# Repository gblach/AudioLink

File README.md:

# AudioLink

AudioLink is a USB and Bluetooth LE Audio receiver with line outputs. Connect it to an amplifier
or active speakers and play music from a computer, a phone or an Auracast broadcast.

https://github.com/user-attachments/assets/b21d6140-ebe1-4f9f-b59c-d1f0c58b71b1

## Features

- **Three sources:** a computer over USB, a phone over Bluetooth LE Audio, or an Auracast
  broadcast.
- **Two 6.35 mm line outputs:** unbalanced stereo or balanced.
- **5-band equalizer**, set from the companion app.
- **Four LEDs that follow the music:** they jump up on loud sounds and fade out in quiet parts.
- **Firmware updates** from the app, over USB or over SWD.
- **Powered from USB-C.** No driver is needed on the computer.

## Hardware

| Part          | Component                                     |
| ------------- | --------------------------------------------- |
| Module        | MinewSemi MS45SF1 (nRF5340, Bluetooth LE)     |
| DAC           | TI PCM5242                                    |
| Output buffer | TI OPA1678                                    |
| LEDs          | 4 x WS2812                                    |
| Outputs       | 2 x 6.35 mm jack (J1, J2)                     |
| Power         | USB-C (J3)                                    |
| PCB           | 4 layers, 100 x 56 mm, all parts on the top   |

## Repository layout

| Path        | Contents                                                             |
| ----------- | -------------------------------------------------------------------- |
| `firmware/` | Zephyr / nRF Connect SDK firmware for both nRF5340 cores             |
| `app/`      | Flutter app (Android, Linux): equalizer, LEDs, firmware update       |
| `pcb/`      | KiCad schematic and PCB, BOM export script, fabrication files        |
| `assets/`   | Release files: firmware hex and DFU images, Android APK; images      |

## Release files

Current release: **0.1.3**.

| File                                                                | Use                                                     |
| ------------------------------------------------------------------- | ------------------------------------------------------- |
| [AudioLink-0.1.3.apk](assets/AudioLink-0.1.3.apk)                   | Android app                                             |
| [AudioLink-0.1.3-dfu.zip](assets/AudioLink-0.1.3-dfu.zip)           | Firmware update over Bluetooth or USB                   |
| [AudioLink-0.1.3-app-core.hex](assets/AudioLink-0.1.3-app-core.hex) | New board over SWD, application core (MCUboot and app)  |
| [AudioLink-0.1.3-net-core.hex](assets/AudioLink-0.1.3-net-core.hex) | New board over SWD, network core (bootloader and radio) |

The version is set in `firmware/VERSION`. The commands below write it as `<ver>`.

## Quick start

1. Plug a USB-C cable into the board.
2. Connect the outputs:
   - **Stereo cable:** use J1 only.
   - **Balanced:** J1 for left, J2 for right. Plugging anything into J2 switches the board to
     balanced mode.
3. Play some music:
   - **From a computer:** select the "AudioLink" sound card.
   - **From a phone:** pair "AudioLink" in the Bluetooth settings. The phone must support LE
     Audio (classic Bluetooth A2DP and iPhones are not supported).
4. Install the [Android app](assets/AudioLink-0.1.3.apk) to set the equalizer and the LEDs.

Without a connected phone, the board joins the first Auracast broadcast it finds.

When several sources play at once, the board picks one:

> USB > phone > Auracast broadcast

## App

The app connects to the board over Bluetooth LE. It sets the equalizer, the LED brightness and
the LED theme, and installs the firmware bundled in the app.

## LEDs

The four LEDs change with the dynamics of the music. They light up at once on a louder sound,
fade over about a second and go dark when the music stops. The level is measured before the
volume, so turning the volume down does not dim them.

In the app you can set:

- **Brightness:** the maximum brightness, from 0% (off) to 100%.
- **Theme:** one of four color pairs.

The small blue LED D5 is the power indicator.

See [LEDs](firmware/README.md#leds) in the firmware README for the LED positions and the
Bluetooth characteristics.

## Flashing and updating

### New board

A new board is flashed over SWD (J-Link on the 10-pin header J4), network core first:

```
nrfutil device recover
nrfutil device program --firmware assets/AudioLink-<ver>-net-core.hex --core Network \
    --options chip_erase_mode=ERASE_ALL
nrfutil device program --firmware assets/AudioLink-<ver>-app-core.hex --core Application \
    --options chip_erase_mode=ERASE_ALL
nrfutil device reset
```

### Board with AudioLink firmware

No probe is needed. Use one of:

- **App:** the update button in the app bar (firmware bundled in the app).
- **nRF Connect Device Manager:** upload `AudioLink-<ver>-dfu.zip` from a paired phone.
- **USB:** `uv run --script firmware/scripts/usb_update.py assets/AudioLink-<ver>-dfu.zip`

The bootloader refuses firmware older than the one running.

## Building

### Firmware

Requirements:

- `nrfutil` with the nRF Connect SDK installed by `nrfutil sdk-manager`
- `just`
- `uv`, for the USB update script

Copy `firmware/.env.example` to `firmware/.env` (not in git) and set the SDK version:

```
NCS_VERSION=v<x.y.z>
# Optional, $HOME/ncs/$NCS_VERSION by default
NCS_DIR=$HOME/ncs/$NCS_VERSION
```

Then, in `firmware/`:

```
just keys    # once, creates the signing keys
just build
```

See [firmware/README.md](firmware/README.md) for all commands, the output modes, LEDs, the
Bluetooth settings service and the update process.

> [!WARNING]
> The signing keys in `firmware/keys/` are not in git. Keep a backup: without them, boards in the
> field can only be updated over SWD.

### App

Bundle the current firmware into the app, then build it with Flutter:

```
cd firmware && just app-firmware
cd ../app && flutter build apk --target-platform android-arm64
```

### Release files

| Copy from                                           | To                               |
| --------------------------------------------------- | -------------------------------- |
| `firmware/build/app/dfu_application.zip`            | `assets/AudioLink-<ver>-dfu.zip` |
| `app/build/app/outputs/flutter-apk/app-release.apk` | `assets/AudioLink-<ver>.apk`     |

The hex files are merged from the build output, see
[Release files](firmware/README.md#release-files) in the firmware README. Then update the links
in [Release files](#release-files) above to the new version.

## PCB

The KiCad project is `pcb/AudioLink.kicad_pro`. A PDF of the schematic is in
`pcb/fab/AudioLink-schematic.pdf`.

- `pcb/fab/` has the fabrication and assembly files, with notes on part substitutions in
  `pcb/fab/README-fab.txt`.
- `pcb/export_bom.py` regenerates `pcb/fab/AudioLink-BOM.csv` from the schematic.

### Enclosure

The board fits the CamdenBoss
[CBHEX1-06-WH](https://www.camdenboss.com/camden-boss/cbhex1-06-wh-hex-box-iot-enclosure-with-6-vented-panels,-white/c-23/p-24194)
Hex-Box enclosure:

- ABS, 146 x 130 x 45 mm outside, 122.5 x 125.5 x 34.5 mm inside
- six removable vented side panels

The jacks J1 and J2 overhang the board edge so they reach a side panel.

## License

| Part                      | License                                                                                              |
| ------------------------- | ---------------------------------------------------------------------------------------------------- |
| Firmware, app and scripts | MIT, see [LICENSE](LICENSE)                                                                          |
| PCB design in `pcb/`      | CERN Open Hardware Licence v2 - Strongly Reciprocal (CERN-OHL-S-2.0), see [pcb/LICENSE](pcb/LICENSE) |

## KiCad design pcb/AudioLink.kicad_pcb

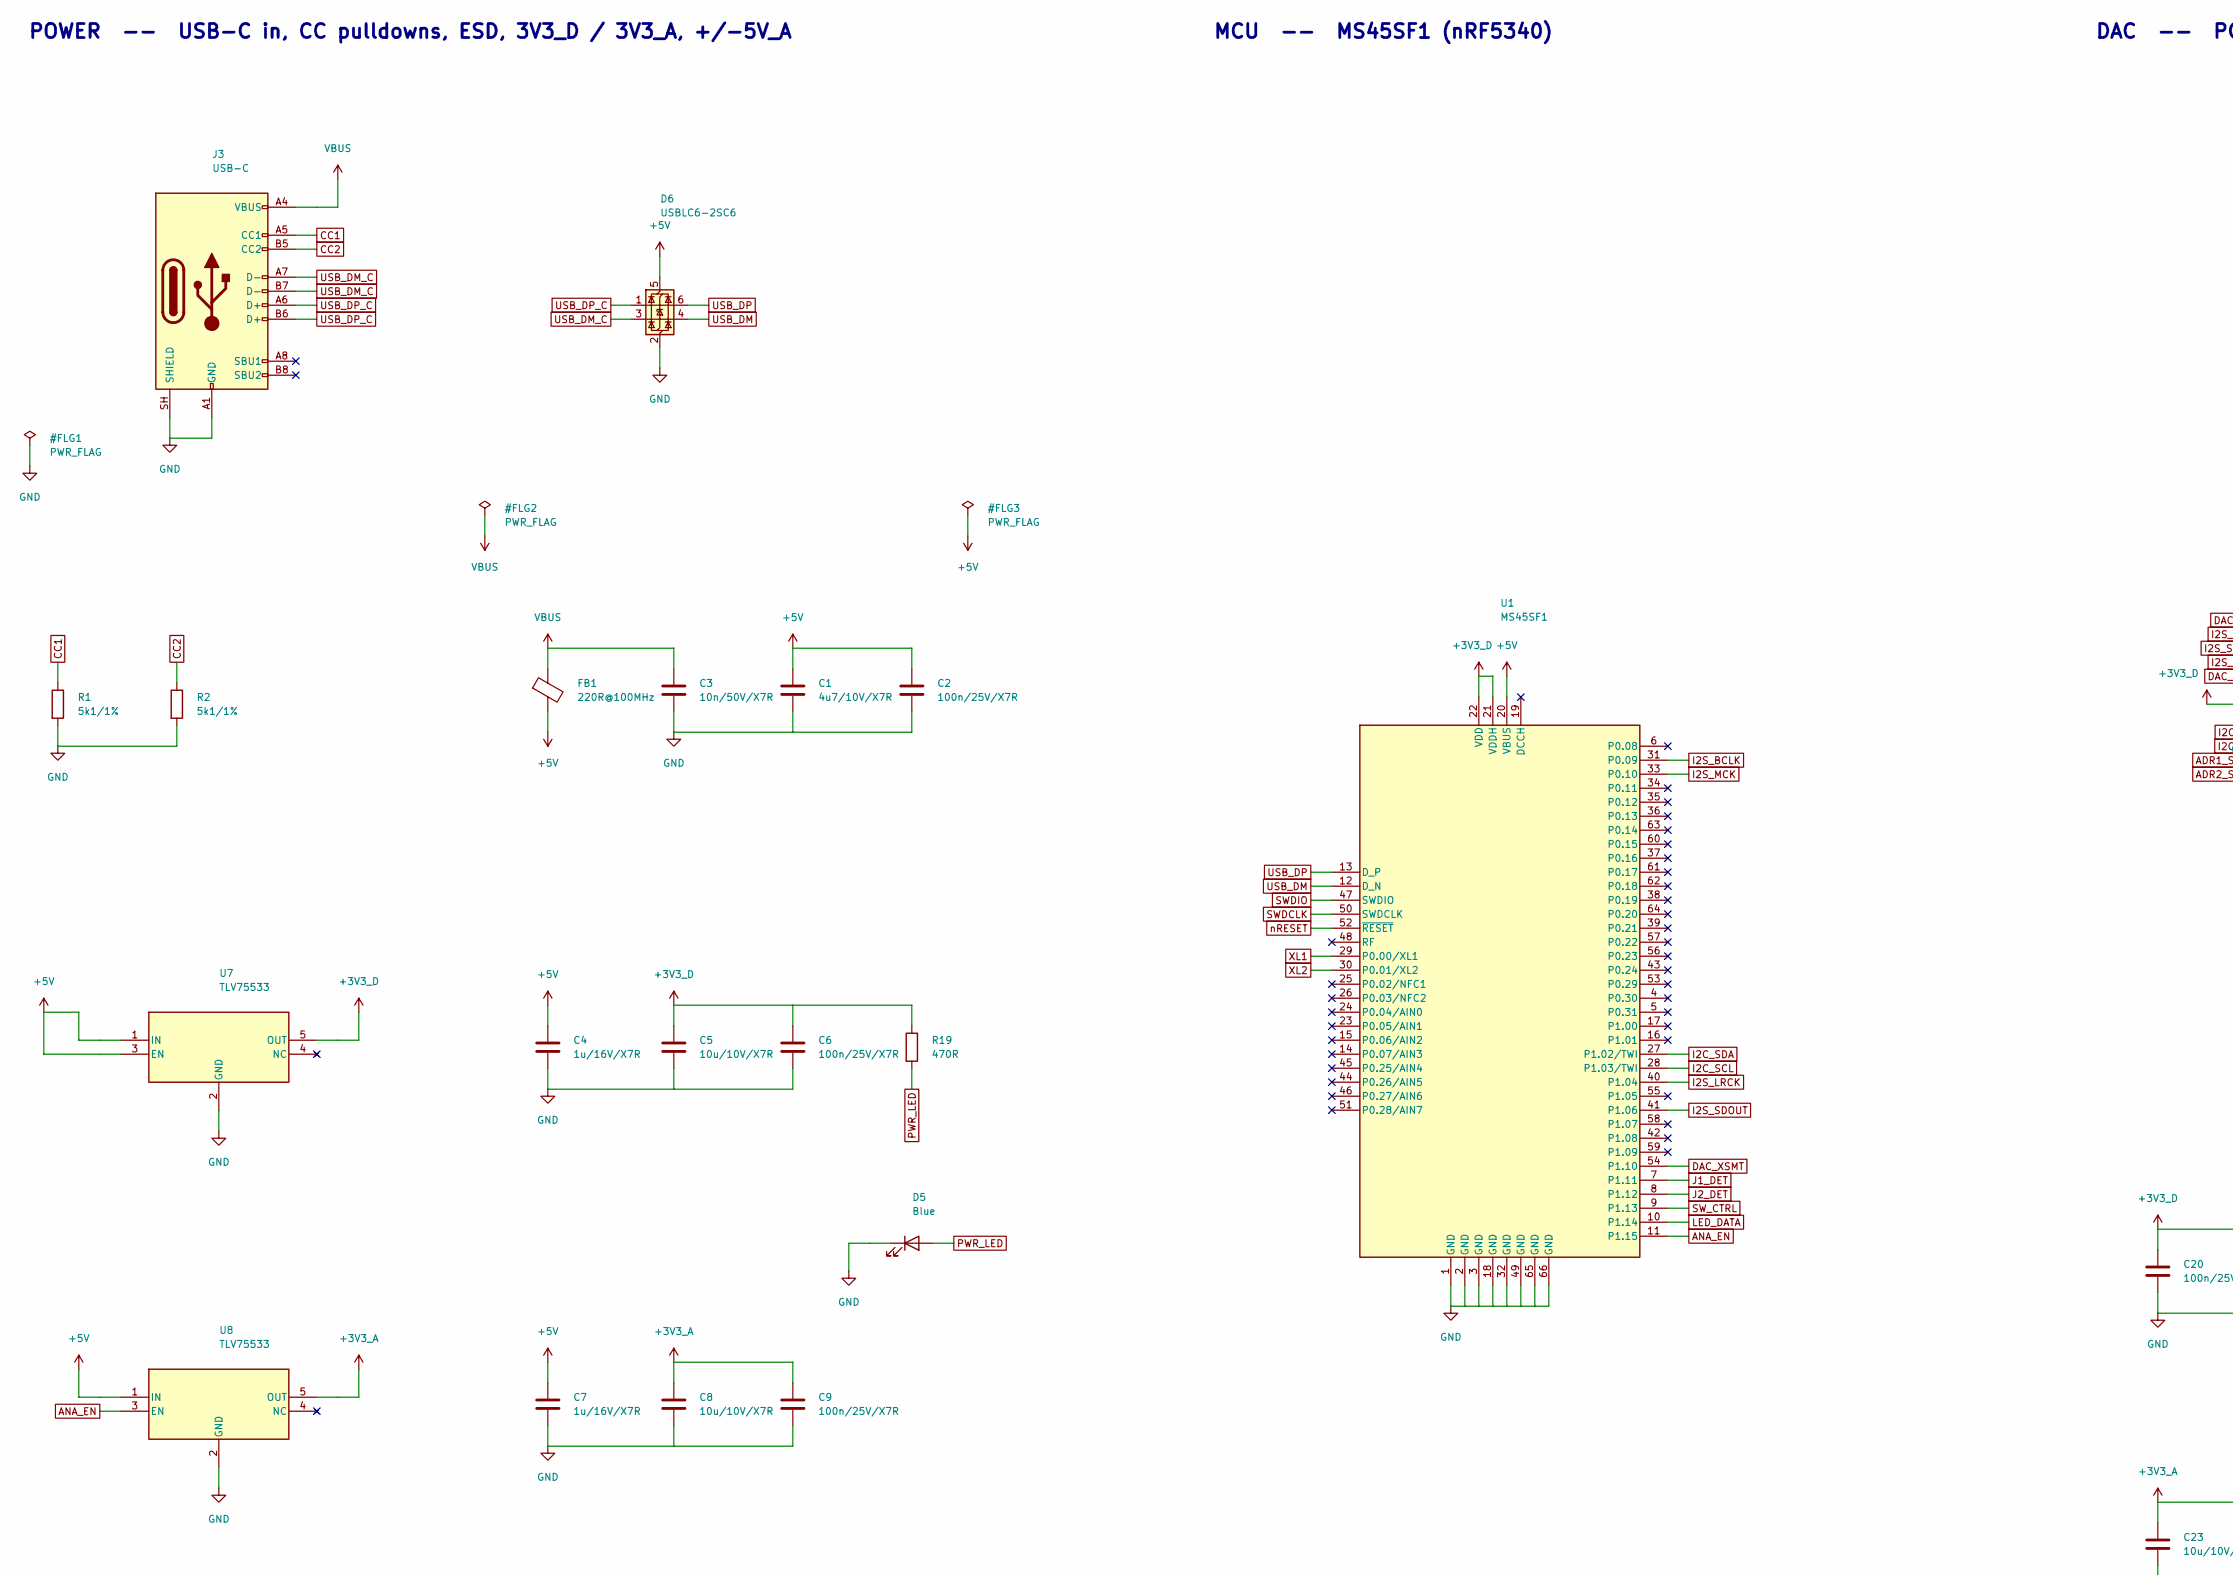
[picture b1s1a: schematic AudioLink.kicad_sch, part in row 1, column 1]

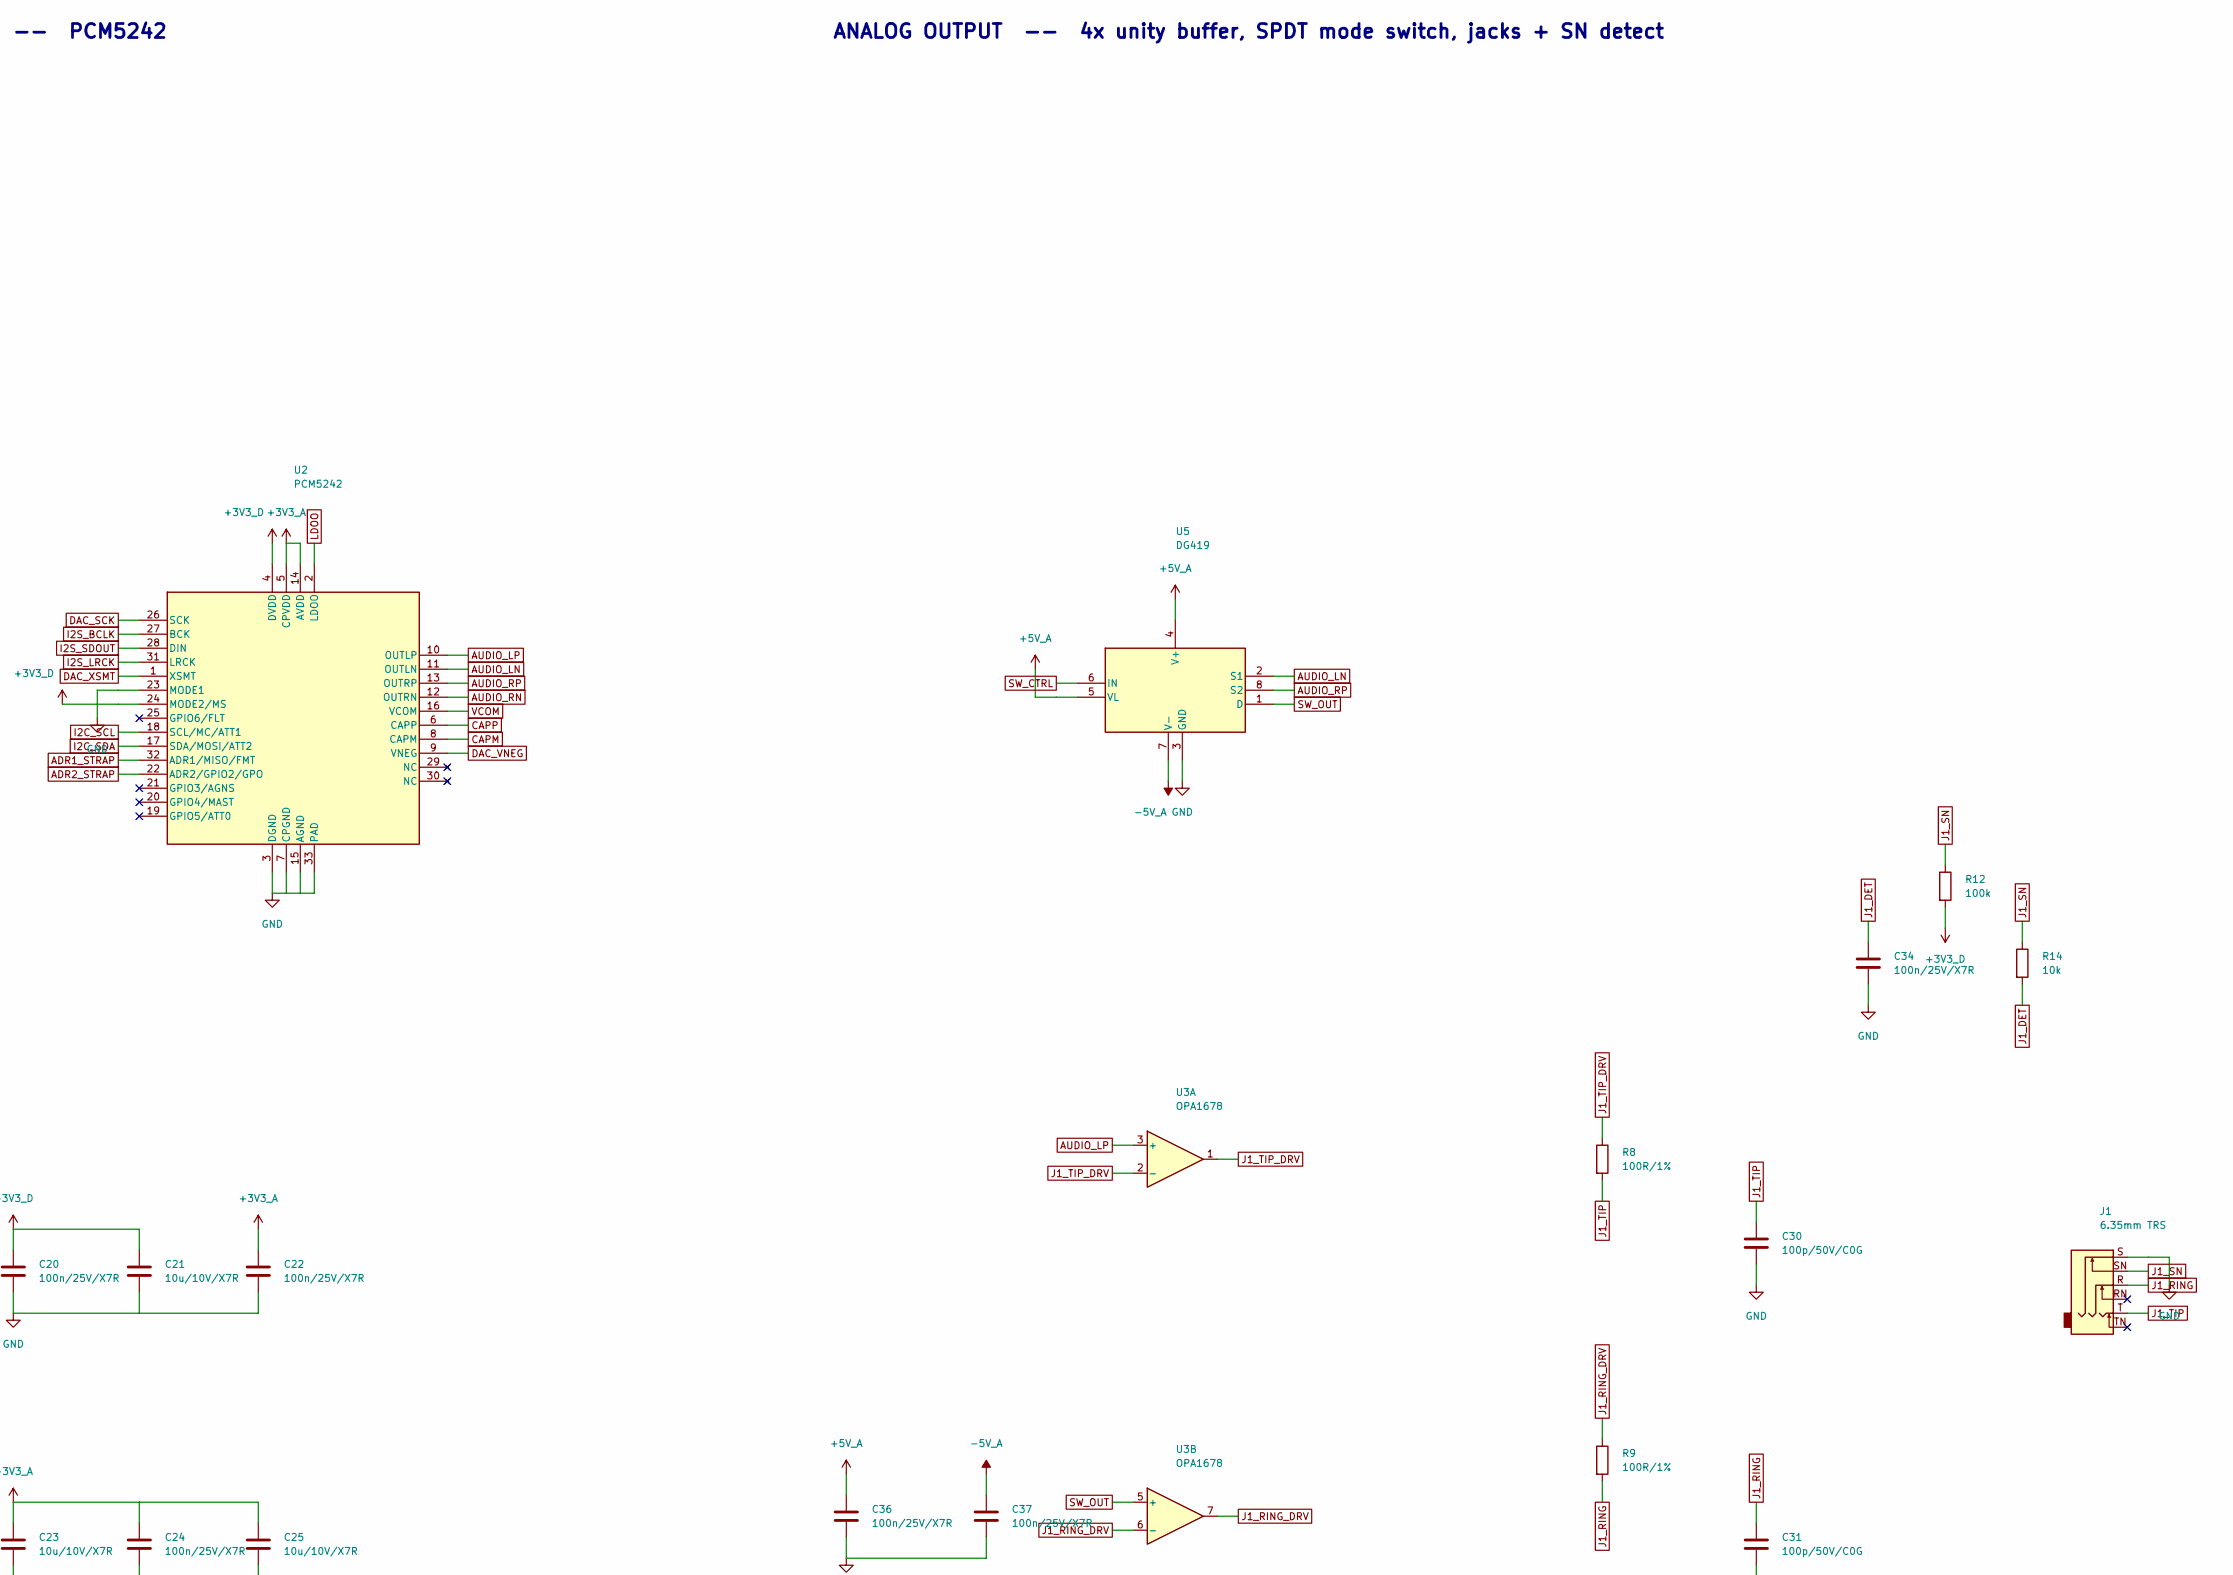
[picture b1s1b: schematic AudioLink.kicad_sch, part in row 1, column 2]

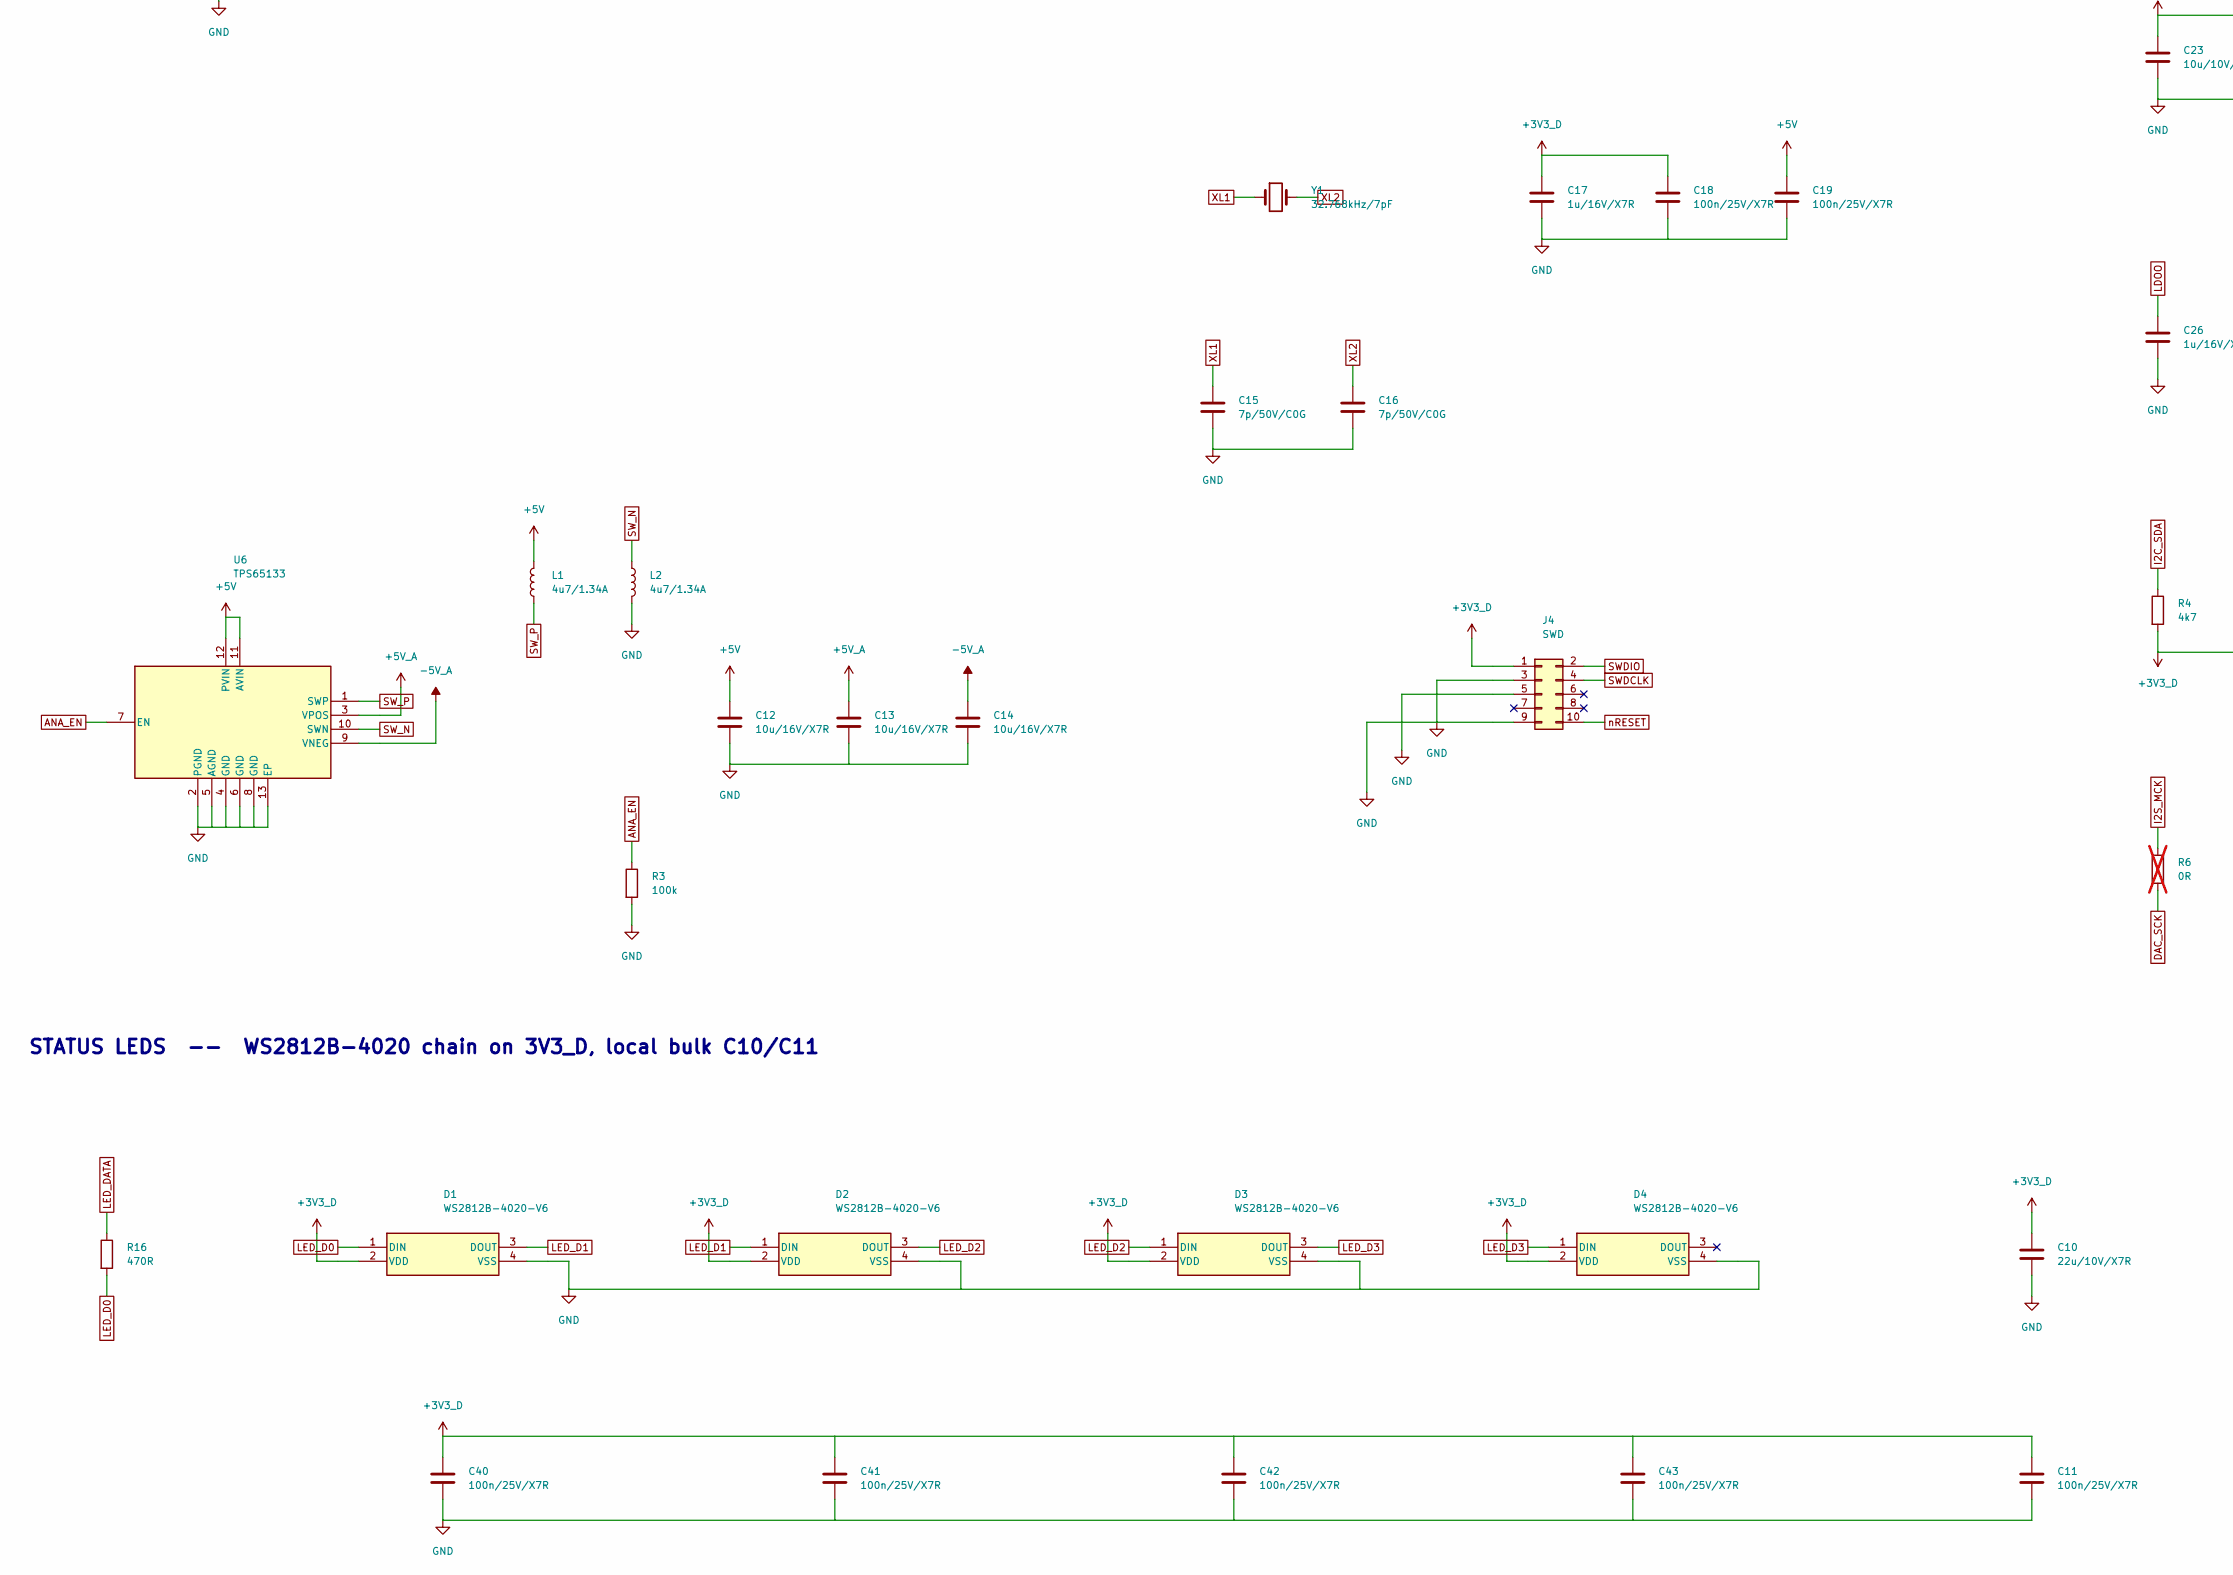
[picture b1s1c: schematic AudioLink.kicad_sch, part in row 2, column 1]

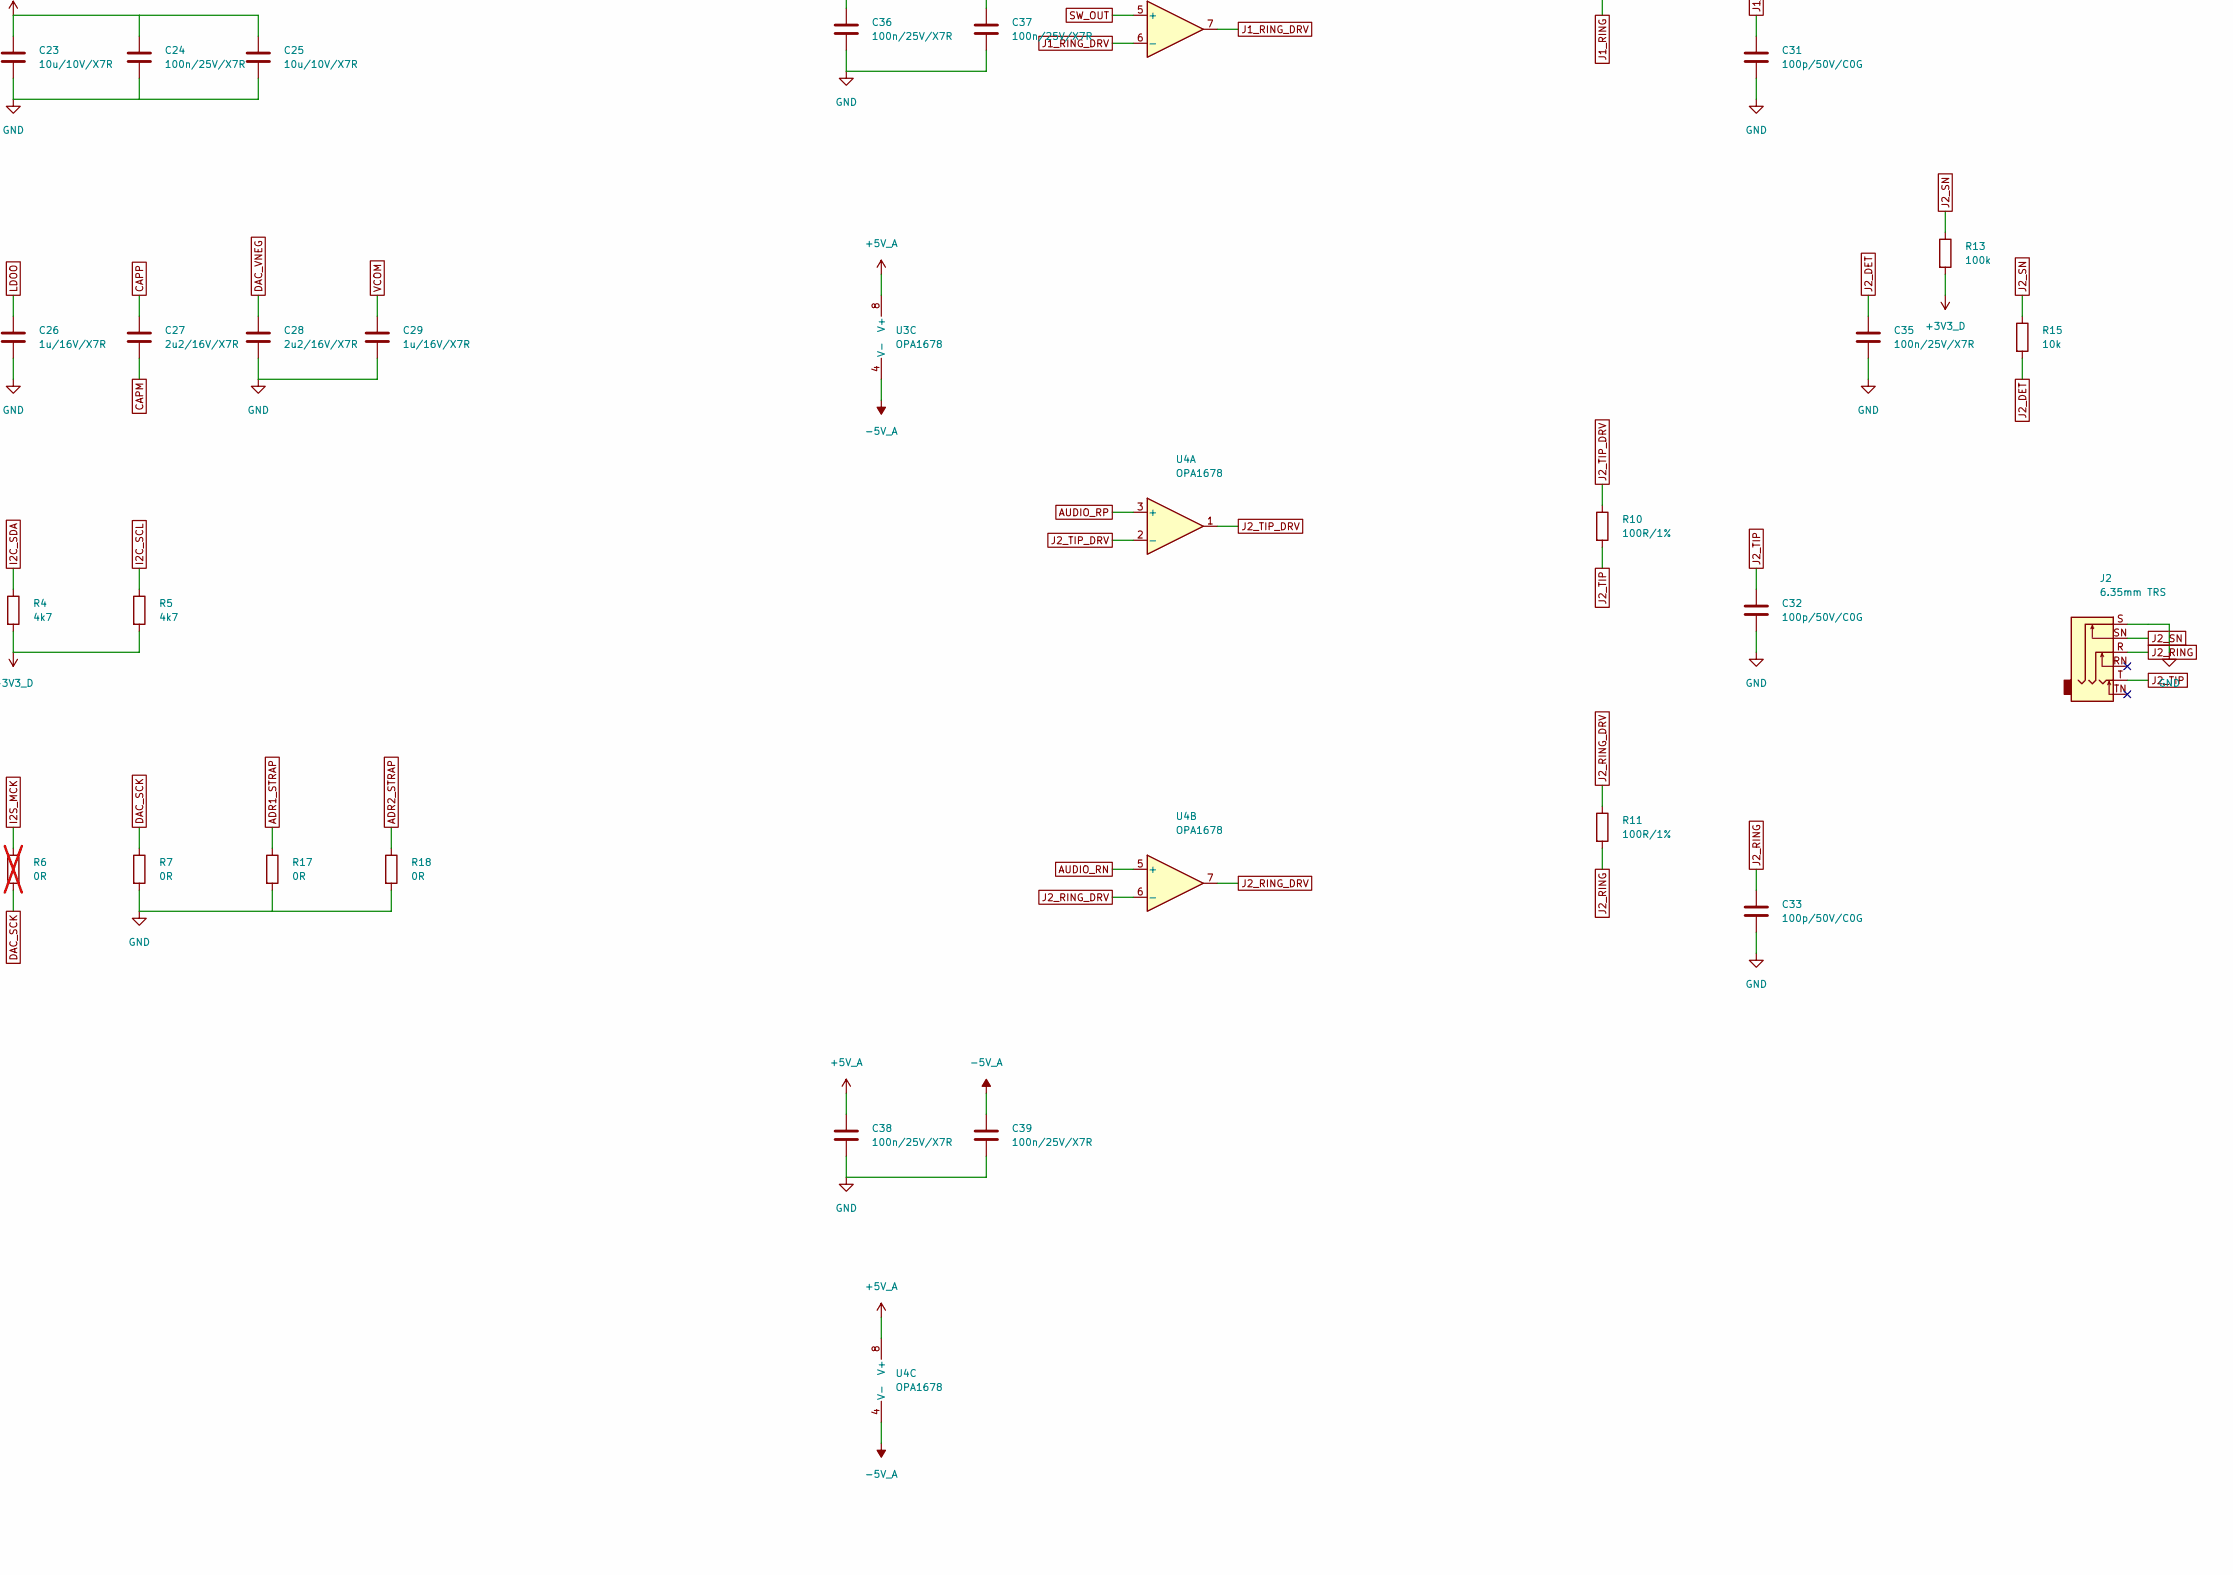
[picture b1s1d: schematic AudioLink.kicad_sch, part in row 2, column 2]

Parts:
C1: 4u7/10V/X7R; C_0805_2012Metric
C2, C6, C9, C11, C18, C19, C20, C22, C24, C34, C35, C36, C37, C38, C39, C40, C41, C42, C43: 100n/25V/X7R; C_0603_1608Metric
C3: 10n/50V/X7R; C_0603_1608Metric
C4, C7, C17, C26, C29: 1u/16V/X7R; C_0603_1608Metric
C5, C8, C21, C23, C25: 10u/10V/X7R; C_0805_2012Metric
C10: 22u/10V/X7R; C_0805_2012Metric
C12, C13, C14: 10u/16V/X7R; C_0805_2012Metric
C15, C16: 7p/50V/C0G; C_0603_1608Metric
C27, C28: 2u2/16V/X7R; C_0603_1608Metric
C30, C31, C32, C33: 100p/50V/C0G; C_0603_1608Metric
D1, D2, D3, D4: WS2812B-4020-V6; LED_WS2812B-4020; MPN WS2812B-4020-V6
D5: Blue; LED_0603_1608Metric; MPN GL0603UB01
D6: USBLC6-2SC6; SOT-23-6; MPN USBLC6-2SC6
FB1: 220R@100MHz; R_0603_1608Metric; MPN BLM18PG221SN1D
J1, J2: 6.35mm TRS; Jack_6.35mm_Neutrik_NRJ6HM-1_TrimCrtYd; MPN NRJ6HM-1
J3: USB-C; USB_C_Receptacle_HCTL_HC-TYPE-C-16P-01A; MPN TYPE-C 16PIN 2MD(073)
J4: SWD; PinHeader_2x05_P1.27mm_Vertical; MPN 62201021621
L1, L2: 4u7/1.34A; L_Bourns-SRN4018; MPN SWPA4020S4R7MT
R1, R2: 5k1/1%; R_0603_1608Metric
R3, R12, R13: 100k; R_0603_1608Metric
R4, R5: 4k7; R_0603_1608Metric
R6: 0R; R_0603_1608Metric; not fitted
R7, R17, R18: 0R; R_0603_1608Metric
R8, R9, R10, R11: 100R/1%; R_0805_2012Metric
R14, R15: 10k; R_0603_1608Metric
R16, R19: 470R; R_0603_1608Metric
U1: MS45SF1; MinewSemi_MS45SF1; MPN MS45SF1-1Y40AIR
U2: PCM5242; VQFN-32-1EP_5x5mm_P0.5mm_EP3.15x3.15mm; MPN PCM5242RHBR
U3, U4: OPA1678; SOIC-8_3.9x4.9mm_P1.27mm; MPN OPA1678IDR
U5: DG419; SOIC-8_3.9x4.9mm_P1.27mm; MPN DG419DY-T1-E3
U6: TPS65133; WSON-12-1EP_3x3mm_P0.5mm_EP1.5x2.5mm; MPN TPS65133DPDR
U7, U8: TLV75533; SOT-23-5; MPN TLV75533PDBVR
Y1: 32.768kHz/7pF; Crystal_SMD_3215-2Pin_3.2x1.5mm; MPN FC-135 32.7680KA-A5

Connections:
+3V3_A: C8.1, C9.1, C22.1, C23.1, C24.1, C25.1, U2.5 (CPVDD), U2.14 (AVDD), U8.5 (OUT)
+3V3_D: C5.1, C6.1, C10.1, C11.1, C17.1, C18.1, C20.1, C21.1, C40.1, C41.1, C42.1, C43.1, D1.2 (VDD), D2.2 (VDD), D3.2 (VDD), D4.2 (VDD), J4.1, R4.2, R5.2, R12.2, R13.2, R19.1, U1.21 (VDDH), U1.22 (VDD), U2.4 (DVDD), U2.24 (MODE2/MS), U7.5 (OUT)
+5V: C1.1, C2.1, C4.1, C7.1, C12.1, C19.1, D6.5 (VBUS), FB1.2, L1.2, U1.20 (VBUS), U6.11 (AVIN), U6.12 (PVIN), U7.1 (IN), U7.3 (EN), U8.1 (IN)
+5V_A: C13.1, C36.1, C38.1, U3.8 (V+), U4.8 (V+), U5.4 (V+), U5.5 (VL), U6.3 (VPOS)
-5V_A: C14.1, C37.1, C39.1, U3.4 (V-), U4.4 (V-), U5.7 (V-), U6.9 (VNEG)
ADR1_STRAP: R17.1, U2.32 (ADR1/MISO/FMT)
ADR2_STRAP: R18.1, U2.22 (ADR2/GPIO2/GPO)
ANA_EN: R3.1, U1.11 (P1.15), U6.7 (EN), U8.3 (EN)
AUDIO_LN: U2.11 (OUTLN), U5.2 (S1)
AUDIO_LP: U2.10 (OUTLP), U3.3 (+)
AUDIO_RN: U2.12 (OUTRN), U4.5 (+)
AUDIO_RP: U2.13 (OUTRP), U4.3 (+), U5.8 (S2)
CAPM: C27.2, U2.8 (CAPM)
CAPP: C27.1, U2.6 (CAPP)
CC1: J3.A5 (CC1), R1.1
CC2: J3.B5 (CC2), R2.1
DAC_SCK: R6.2, R7.1, U2.26 (SCK)
DAC_VNEG: C28.1, U2.9 (VNEG)
DAC_XSMT: U1.54 (P1.10), U2.1 (XSMT)
GND: C1.2, C2.2, C3.2, C4.2, C5.2, C6.2, C7.2, C8.2, C9.2, C10.2, C11.2, C12.2, C13.2, C14.2, C15.2, C16.2, C17.2, C18.2, C19.2, C20.2, C21.2, C22.2, C23.2, C24.2, C25.2, C26.2, C28.2, C29.2, C30.2, C31.2, C32.2, C33.2, C34.2, C35.2, C36.2, C37.2, C38.2, C39.2, C40.2, C41.2, C42.2, C43.2, D1.4 (VSS), D2.4 (VSS), D3.4 (VSS), D4.4 (VSS), D5.1 (K), D6.2 (GND), J1.S, J2.S, J3.A1 (GND), J3.A12 (GND), J3.B1 (GND), J3.B12 (GND), J3.SH (SHIELD), J4.3, J4.5, J4.9, L2.2, R1.2, R2.2, R3.2, R7.2, R17.2, R18.2, U1.1 (GND), U1.2 (GND), U1.3 (GND), U1.18 (GND), U1.32 (GND), U1.49 (GND), U1.65 (GND), U1.66 (GND), U2.3 (DGND), U2.7 (CPGND), U2.15 (AGND), U2.23 (MODE1), U2.33 (PAD), U5.3 (GND), U6.2 (PGND), U6.4 (GND), U6.5 (AGND), U6.6 (GND), U6.8 (GND), U6.13 (EP), U7.2 (GND), U8.2 (GND); also elsewhere on the board
I2C_SCL: R5.1, U1.28 (P1.03/TWI), U2.18 (SCL/MC/ATT1)
I2C_SDA: R4.1, U1.27 (P1.02/TWI), U2.17 (SDA/MOSI/ATT2)
I2S_BCLK: U1.31 (P0.09), U2.27 (BCK)
I2S_LRCK: U1.40 (P1.04), U2.31 (LRCK)
I2S_MCK: R6.1, U1.33 (P0.10)
I2S_SDOUT: U1.41 (P1.06), U2.28 (DIN)
J1_DET: C34.1, R14.2, U1.7 (P1.11)
J1_RING: C31.1, J1.R, R9.2
J1_RING_DRV: R9.1, U3.6 (-), U3.7
J1_SN: J1.SN, R12.1, R14.1
J1_TIP: C30.1, J1.T, R8.2
J1_TIP_DRV: R8.1, U3.1, U3.2 (-)
J2_DET: C35.1, R15.2, U1.8 (P1.12)
J2_RING: C33.1, J2.R, R11.2
J2_RING_DRV: R11.1, U4.6 (-), U4.7
J2_SN: J2.SN, R13.1, R15.1
J2_TIP: C32.1, J2.T, R10.2
J2_TIP_DRV: R10.1, U4.1, U4.2 (-)
LDOO: C26.1, U2.2 (LDOO)
LED_D0: D1.1 (DIN), R16.2
LED_D1: D1.3 (DOUT), D2.1 (DIN)
LED_D2: D2.3 (DOUT), D3.1 (DIN)
LED_D3: D3.3 (DOUT), D4.1 (DIN)
LED_DATA: R16.1, U1.10 (P1.14)
PWR_LED: D5.2 (A), R19.2
SWDCLK: J4.4, U1.50 (SWDCLK)
SWDIO: J4.2, U1.47 (SWDIO)
SW_CTRL: U1.9 (P1.13), U5.6 (IN)
SW_N: L2.1, U6.10 (SWN)
SW_OUT: U3.5 (+), U5.1 (D)
SW_P: L1.1, U6.1 (SWP)
USB_DM: D6.4 (I/O2), U1.12 (D_N)
USB_DM_C: D6.3 (I/O2), J3.A7 (D-), J3.B7 (D-)
USB_DP: D6.6 (I/O1), U1.13 (D_P)
USB_DP_C: D6.1 (I/O1), J3.A6 (D+), J3.B6 (D+)
VBUS: C3.1, FB1.1, J3.A4 (VBUS), J3.A9 (VBUS), J3.B4 (VBUS), J3.B9 (VBUS)
VCOM: C29.1, U2.16 (VCOM)
XL1: C15.1, U1.29 (P0.00/XL1), Y1.1
XL2: C16.1, U1.30 (P0.01/XL2), Y1.2
nRESET: J4.10, U1.52 (~RESET)

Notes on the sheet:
POWER -- USB-C in, CC pulldowns, ESD, 3V3_D / 3V3_A, +/-5V_A
MCU -- MS45SF1 (nRF5340)
DAC -- PCM5242
ANALOG OUTPUT -- 4x unity buffer, SPDT mode switch, jacks + SN detect
STATUS LEDS -- WS2812B-4020 chain on 3V3_D, local bulk C10/C11
